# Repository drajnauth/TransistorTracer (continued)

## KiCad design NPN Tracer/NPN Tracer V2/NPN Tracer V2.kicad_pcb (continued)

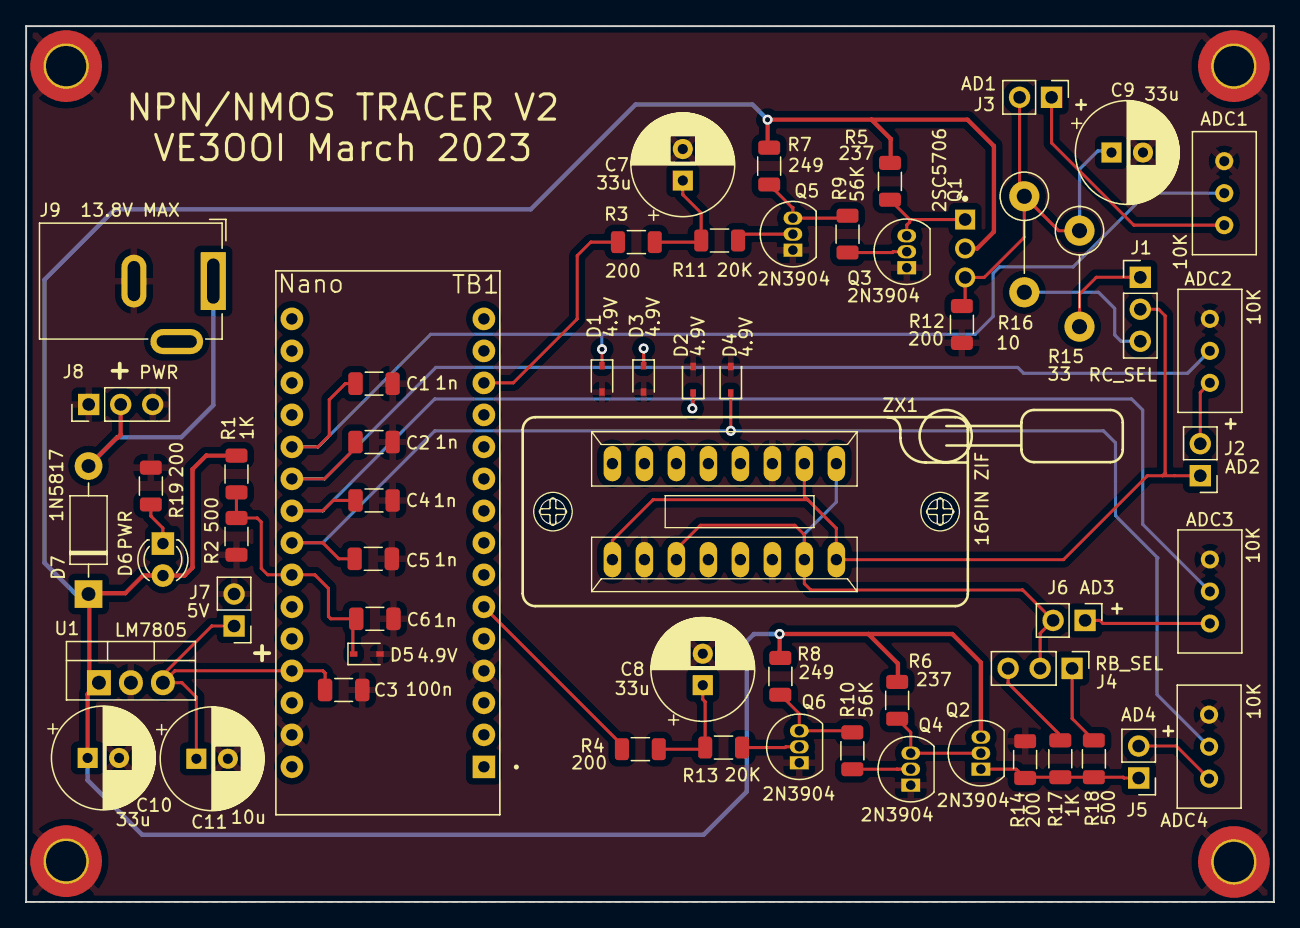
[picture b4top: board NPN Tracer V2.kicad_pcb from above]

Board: 2 copper layers, 99.1 x 69.5 mm, 63 parts (0 on the bottom side), 34 nets.

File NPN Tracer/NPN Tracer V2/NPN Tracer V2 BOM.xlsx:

Component Count: | 59
Ref | Qnty | Value | Cmp name | Footprint | Description
ADC1, ADC2, ADC3, ADC4, | 4 | 10K | R_Potentiometer_Trim | Potentiometer_THT:Potentiometer_Bourns_3296W_Vertical | Trim-potentiometer
C1, C2, C4, C5, C6, | 5 | 1n | C | Capacitor_SMD:C_1206_3216Metric | Unpolarized capacitor
C11, | 1 | 10u | C_Polarized | Capacitor_THT:CP_Radial_D8.0mm_P2.50mm | Polarized capacitor
C3, | 1 | 100n | C | Capacitor_SMD:C_1206_3216Metric | Unpolarized capacitor
C7, C8, C9, C10, | 4 | 33u | C_Polarized | Capacitor_THT:CP_Radial_D8.0mm_P2.50mm | Polarized capacitor
D1, D2, D3, D4, D5, | 5 | 4.9V | D_Zener | Diode_SMD:D_SOD-323 | Zener diode
D6, | 1 | PWR | LED | LED_THT:LED_D3.0mm | Light emitting diode
D7, | 1 | 1N5817 | 1N5817 | Diode_THT:D_DO-41_SOD81_P10.16mm_Horizontal | 20V 1A Schottky Barrier Rectifier Diode, DO-41
J1, | 1 | RC_SEL | Conn_01x03 | Connector_PinHeader_2.54mm:PinHeader_1x03_P2.54mm_Vertical | Generic connector, single row, 01x03, script generated (kicad-library-utils/sch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
J2, | 1 | AD2 | Conn_01x02 | Connector_PinHeader_2.54mm:PinHeader_1x02_P2.54mm_Vertical | Generic connector, single row, 01x02, script generated (kicad-library-utils/sch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
J3, | 1 | AD1 | Conn_01x02 | Connector_PinHeader_2.54mm:PinHeader_1x02_P2.54mm_Vertical | Generic connector, single row, 01x02, script generated (kicad-library-utils/sch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
J4, | 1 | RB_SEL | Conn_01x03 | Connector_PinHeader_2.54mm:PinHeader_1x03_P2.54mm_Vertical | Generic connector, single row, 01x03, script generated (kicad-library-utils/sch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
J5, | 1 | AD4 | Conn_01x02 | Connector_PinHeader_2.54mm:PinHeader_1x02_P2.54mm_Vertical | Generic connector, single row, 01x02, script generated (kicad-library-utils/sch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
J6, | 1 | AD3 | Conn_01x02 | Connector_PinHeader_2.54mm:PinHeader_1x02_P2.54mm_Vertical | Generic connector, single row, 01x02, script generated (kicad-library-utils/sch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
J7, | 1 | 5V | Conn_01x02 | Connector_PinHeader_2.54mm:PinHeader_1x02_P2.54mm_Vertical | Generic connector, single row, 01x02, script generated (kicad-library-utils/sch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
J8, | 1 | PWR | Conn_01x03 | Connector_PinHeader_2.54mm:PinHeader_1x03_P2.54mm_Vertical | Generic connector, single row, 01x03, script generated (kicad-library-utils/sch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
J9, | 1 | 13.8V MAX | Barrel_Jack | Connector_BarrelJack:BarrelJack_GCT_DCJ200-10-A_Horizontal | DC Barrel Jack
Q1, | 1 | 2SC5706 | 2SC5706-E | Custom_RF:2SC5706
Q2, Q3, Q4, Q5, Q6, | 5 | 2N3904 | 2N3904 | Package_TO_SOT_THT:TO-92_Inline | 0.2A Ic, 40V Vce, Small Signal NPN Transistor, TO-92
R1, R17, | 2 | 1K | R_US | Resistor_SMD:R_1206_3216Metric | Resistor, US symbol
R11, R13, | 2 | 20K | R_US | Resistor_SMD:R_1206_3216Metric | Resistor, US symbol
R15, | 1 | 33 | R_US | Resistor_THT:R_Axial_DIN0411_L9.9mm_D3.6mm_P7.62mm_Vertical | Resistor, US symbol
R16, | 1 | 10 | R_US | Resistor_THT:R_Axial_DIN0411_L9.9mm_D3.6mm_P7.62mm_Vertical | Resistor, US symbol
R2, R18, | 2 | 500 | R_US | Resistor_SMD:R_1206_3216Metric | Resistor, US symbol
R3, R4, R12, R14, R19, | 5 | 200 | R_US | Resistor_SMD:R_1206_3216Metric | Resistor, US symbol
R5, R6, | 2 | 237 | R_US | Resistor_SMD:R_1206_3216Metric | Resistor, US symbol
R7, R8, | 2 | 249 | R_US | Resistor_SMD:R_1206_3216Metric | Resistor, US symbol
R9, R10, | 2 | 56K | R_US | Resistor_SMD:R_1206_3216Metric | Resistor, US symbol
TB1, | 1 | Nano | ARDUINO_NANO | Microcontrollers:SHIELD_ARDUINO_NANO
U1, | 1 | LM7805 | LM7805_TO220 | Package_TO_SOT_THT:TO-220-3_Vertical | Positive 1A 35V Linear Regulator, Fixed Output 5V, TO-220
ZX1, | 1 | 16PIN ZIF | 16Pin ZIF | Custom_RF:16Pin ZIF

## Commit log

2023-03-29 Initial Hardware Files
2023-03-29 Initial Software Files for V1
2023-03-29 Initial Documentation Files
2023-03-29 Initial Simulation Files
2023-03-30 Add Python Graphing Program
2023-03-30 Code update 30Mar23
2023-04-01 Update 31Mar23
2023-04-06 6Apr12 Update
2023-04-07 Update 7Mar23
2023-04-09 Update 9Mar23
2023-04-10 Update 9Apr23
2023-05-07 Update 7May23
2023-05-08 Update 8May23
2023-05-17 Add PDF
